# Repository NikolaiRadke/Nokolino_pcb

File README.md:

The ATtiny-based litte brother of Noko. Tiny and cute. And everyone is invited to **contribute**. Nokolino is for everyone. This repository is for the **PCB** version of Nokolino, easy and fast to build. See [PCB](https://github.com/NikolaiRadke/NOKOlino_2/tree/master/PCB.md) on how to get your own boards. Do you own a complete kit? Look [here](https://github.com/NikolaiRadke/Nokolino).    
  
What's new? See the [newsblog](https://github.com/NikolaiRadke/NOKOlino_2/tree/master/NEWS.md).   

Like his big brother **Noko**, the little Nokolino delights it's surroundings with cheeky comments. But unlike Noko he is more obstinate - no radio, a display, no frills. Instead of an Arduino he has a small **ATtiny** microcontroller, only an on-off switch and a big button. But he is small, can stay active for days and is, in contrast to his big brother, very easy to build.  
  
Another useful application option would be to use the hardware without the monster suit as a **music box** in an old used doll to bring it back to modern days, maybe with other sounds or songs.  

What does he to - technically? Whenever you press his button, he will laugh. And when he's just turned on, he says something random randomly every statistically 10 minutes. That's ist. Quite a lot for a stuffed monster!  
  
**Nokolino** stands for **No**ra and Ni**ko**s monster - the appendix **lino** describes the small version.  
  
### Notes for non-German Nokolino makers  
  
Right now, the building wiki, the voice set and the manual are in German. I'll try to translate the wiki and the manual one day. Until then, feel free to ask me for translation, if you need help. **Contribute!** I need an English voice set and English text files. In addition, any other language is welcome, Nokolino is to be cosmopolitan!
  
### Prerequisites
  
Nokolino needs Arduino IDE 1.6.6 or newer (https://www.arduino.cc/en/Main/Software). Copy the folder `Nokolino/src/Nokolino_V30/` for the **JQ6500** module, `Nokolino/src//Nokolino_V31/` for the **JQ8400** module, `Nokolino/src/Nokolino_V32/`for the **DFPlayer** module or `Nokolino/src/Nokolino_V21/` for **older 2018 kits** into your sketch folder and install ATtiny support. See [how to compile](https://github.com/NikolaiRadke/Nokolino_pcb/tree/master/howto_compile) for further instructions. 
  
### Content

```
Nokolino/
├── howto_compile/
|   Manual how compile the sketches in your Arduino IDE.
|
├── linux_uploader/
|   Tool for uploading MP3-files to the JQ6500.
|
├── manual/
|   Nokolino manuals in PDF format.
|
├── mp3/
|   Voice sets for 32MBit- & 16MBit modules in German. English needed? Contribute!
|   ├── Nokolino/
|   |   Male voice sets, spoken by Carsten Caniglia.
|   |   ├── 2MB/
|   |   |   80 files for smaller (16 MBit) modules.
|   |   └── 4MB/
|   |       164 files for recommended (32 MBit) modules.
|   └── Nokolina/
|       Female voice set, spoken by Norma Anthes
|       ├── 2MB/
|       |   80 files for smaller (16 MBit) modules.
|       └── 4MB/
|           164 files for recommended (32 MBit) modules.
|
├── schematics/
|   The circuit diagrams, 3D cab model and sewing pattern.  
|   └── gerber/
|       The gerber files for the PCB to build by your own.
|       ├── V30/
|       |   The gerbers for the JQ6500 module.
|       ├── V31/
|       |   The gerbers for the JQ8400 module.
|       └── V32/
|           The gerbers for the DFPlayer module.
|
└── src/
    ATtiny sketches
    ├── Nokolino_V21/
    |   Old software for old 2018 kits.
    ├── Nokolino_V30/
    |   The sketch for the JQ6500 module.
    ├── Nokolino_V31/
    |   The sketch for the JQ8400 module.
    └── Nokolino_V32/
        The sketch for the DFPlayer module.
```
### Let's get started!

Interested in Nokolino? Great! Let's start here: [German wiki](https://github.com/NikolaiRadke/Nokolino_pcb/wiki).  
English wiki will follow. One day...

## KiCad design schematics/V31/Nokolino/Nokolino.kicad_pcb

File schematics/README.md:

# Schematics

* **Nokolino_V32.pdf** Nokolnio's circuit diagram for the DFPlayer module.
* **Nokolino_V31.pdf** Nokolino's circuit diagram for the JQ8400 module.  
* **Nokolino_V30.pdf** Nokolino's circuit diagram for the JQ6500 module.  
* **M2_button_cab.stl** The 3D model for the button cabs for self printing.  
* **Nokolino_Pattern.pdf** Nokolino's sewing pattern.  
* **/gerber**  The folder for the gerber files needed to print your own PCBs.

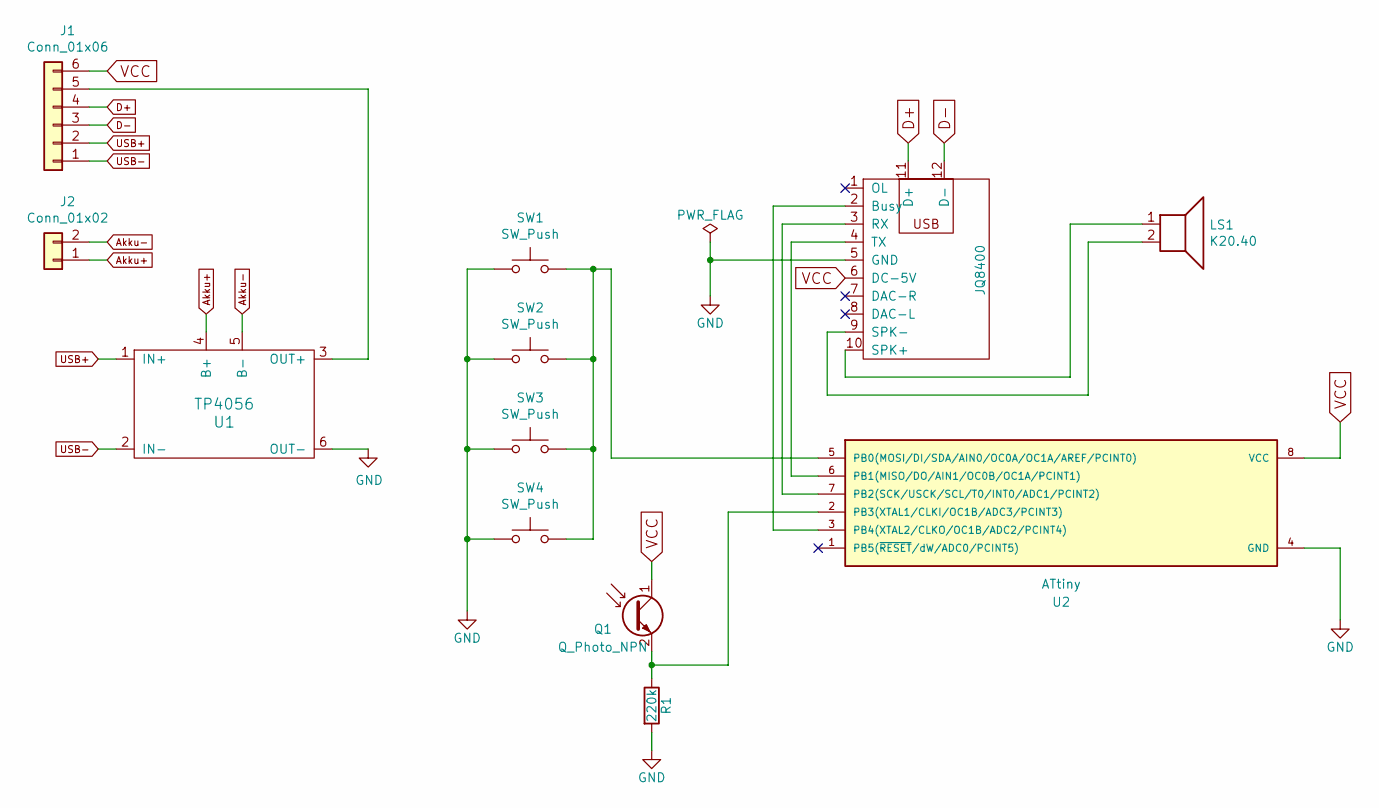
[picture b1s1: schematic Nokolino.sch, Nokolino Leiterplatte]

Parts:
J1: Conn_01x06; PinHeader_1x06_P2.54mm_Vertical
J2: Conn_01x02; PinHeader_1x02_P2.54mm_Vertical
LS1: K20.40
Q1: Q_Photo_NPN; PinHeader_1x02_P2.54mm_Vertical
R1: 220k; R_Axial_DIN0207_L6.3mm_D2.5mm_P7.62mm_Horizontal
SW1, SW2, SW3, SW4: SW_Push; SW_PUSH_6mm_H13mm
U1: TP4056; TP4056-Protect
U2: ATtiny; ATTINY85-20PU
U3: JQ8400; JQ8400-10p

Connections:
Akku+: J2.1, U1.4 (B+)
Akku-: J2.2, U1.5 (B-)
D+: J1.4, U3.11 (D+)
D-: J1.3, U3.12 (D-)
GND: R1.2, SW1.1, SW2.1, SW3.1, SW4.1, U1.6 (OUT-), U2.4 (GND), U3.5 (GND)
unnamed: J1.5, U1.3 (OUT+)
unnamed: LS1.1, U3.10 (SPK+)
unnamed: LS1.2, U3.9 (SPK-)
unnamed: Q1.2 (E), R1.1, U2.2 (PB3(XTAL1/CLKI/OC1B/ADC3/PCINT3))
unnamed: SW1.2, SW2.2, SW3.2, SW4.2, U2.5 (PB0(MOSI/DI/SDA/AIN0/OC0A/OC1A/AREF/PCI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)
unnamed: U2.3 (PB4(XTAL2/CLKO/OC1B/ADC2/PCINT4)), U3.2 (Busy)
unnamed: U2.6 (PB1(MISO/DO/AIN1/OC0B/OC1A/PCINT1)), U3.4 (TX)
unnamed: U2.7 (PB2(SCK/USCK/SCL/T0/INT0/ADC1/PCINT2)), U3.3 (RX)
USB+: J1.2, U1.1 (IN+)
USB-: J1.1, U1.2 (IN-)
VCC: J1.6, Q1.1 (C), U2.8 (VCC), U3.6 (DC-5V)

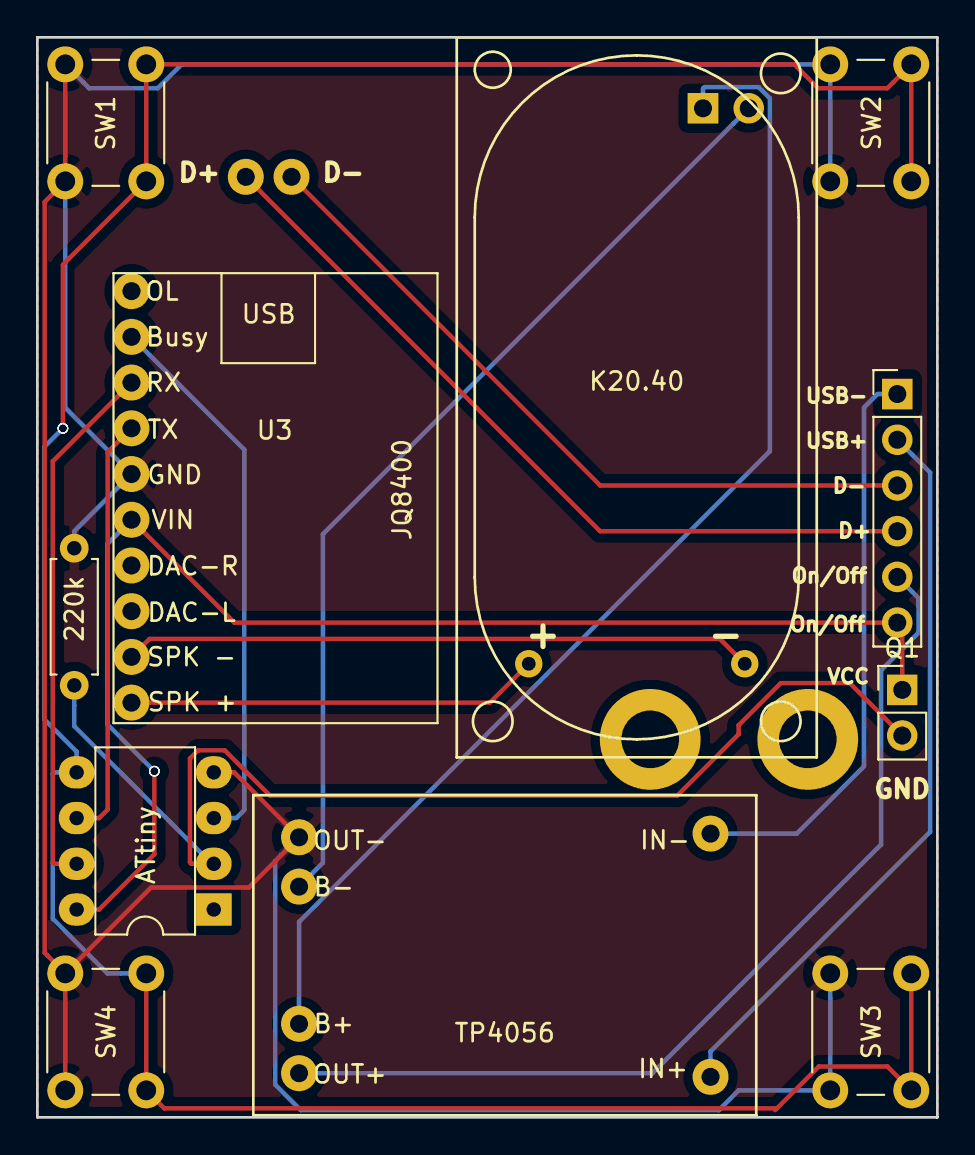
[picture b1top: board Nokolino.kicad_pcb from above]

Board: 2 copper layers, 50.0 x 60.0 mm, 14 parts (1 on the bottom side), 16 nets.

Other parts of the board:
MH1: MH1; MountingHole_3.2mm_M3_DIN965_Pad
MH2: MH2; MountingHole_3.2mm_M3_DIN965_Pad

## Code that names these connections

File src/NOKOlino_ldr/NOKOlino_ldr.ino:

/* NOKOlino V1.0 24.05.2018 - Nikolai Radke
 *  
 *  Sketch for Mini-NOKO-Monster
 *  for Attiny45/85 | 8 Mhz - remember to flash your bootloader first!
 *  SoftwareSerial needs 8 MHz to work correctly.
 *  
 *  Flash-Usage: 3.724 (1.8.2 | ATTiny 1.0.2 | Linux X86_64 | ATtiny85)
 *  
 *  Circuit:
 *  1: RST | PB5  free
 *  2: A3  | PB3  SFH300          
 *  3: A2  | PB4  Busy JQ6500 - 8
 *  4: GND        GND
 *  5: D0  | PB0  free
 *  6: D1  | PB1  RX JQ6500   - 9   
 *  7: D2  | PB2  Button      - GND
 *  8: VCC        VCC
 *  
 *  Sleepmodes:
 *  0=16ms, 1=32ms, 2=64ms, 3=128ms, 4=250ms, 5=500ms
 *  6=1sec, 7=2sec, 8=4sec, 9=8sec
 */

#include <avr/sleep.h>
#include <avr/interrupt.h>
#include <SoftwareSerial.h>
#include <EEPROM.h>

//--------------------------------------------------------------------------------
// Configuation
#define Time         10             // Say something every statistical 10 minutes
#define Volume       25             // Volume 0-30 - 20 is recommended 

#define Breadboard                // Breadboard or PCB?

// Voice set selection
//#define Set_8MBit_16MBit
#define Set_32MBit
//#define Set_own

#ifdef Set_8MBit_16MBit
  #define Button_event 30           // Last button event number (30.mp3)
  #define Time_event   79           // Last time event number (79.mp3)
#endif
#ifdef Set_32MBit
  #define Button_event 40
  #define Time_event   163
#endif
#ifdef Set_own
  #define Button_event 0
  #define Time_event   0
#endif

#ifdef Breadboard
  #define Offset       0.4          // Battery measuring error
  #define maxInput     50           // Max. value from busy line. 
#else
  #define Offset       0.6
  #define maxInput     0
#endif

// Optional - comment out with // to disable
#define Batterywarning             // NOKOlino gives a warning when battery is low
//---------------------------------------------------------------------------------

// Optional battery warning
#define minCurrent   3.50 +Offset   // Low power warning current + measuring error
#define battLow      3.30 +Offset   // Minimal voltage before JQ6500 fails

// Hardware pins
#define TX      0
#define RX      1
#define Busy    2

// ADC and BOD
#ifndef cbi
  #define cbi(sfr, bit) (_SFR_BYTE(sfr) &= ~_BV(bit))
#endif
#ifndef sbi
  #define sbi(sfr, bit) (_SFR_BYTE(sfr) |= _BV(bit))
#endif
#define BODS 7                       // BOD sleep bit in MCUCR
#define BODSE 2                      // BOD sleep enable bit in MCUCR

// Variables
uint16_t address,seed;
volatile boolean f_wdt = 1;          // Volatile -> it is an interrupt routine
boolean low=false;

SoftwareSerial mp3(TX,RX);           // TX to D0, RX to D1

int main(void) {

#ifdef Batterywarning
  uint16_t current;
  double vref;
  uint16_t counter=10;               // Check shortly after startup
#endif

init(); 
{
  // Power saving
  MCUCR |= _BV(BODS) | _BV(BODSE);   // Disable brown out detection - default?
  ACSR |= _BV(ACD);                  // Disable analog comparator - default?
  DDRB &= ~(1<<PB2);                 // D2 INPUT
  PORTB |= (1<<PB2);                 // D2 HIGH 

  pinMode(0,OUTPUT);
  digitalWrite(0,LOW);
  
  // Start JQ6500
  mp3.begin(9600);
  mp3.write("\x7E\x02\x0C\xEF");     // Reset JQ6500
  setup_watchdog(5);                 // Sleep 500ms
  attiny_sleep();                 
  mp3.write("\x7E\x03\x06");
  mp3.write(Volume);                 // Set volume
  mp3.write("\xEF"); 
  setup_watchdog(3);
  attiny_sleep();                    // Sleep 128ms
  mp3.write("\x7E\x03\x11\x04\xEF"); // No loop
  attiny_sleep();                    // Sleep 128ms
  mp3.write("\x7E\x02\x0A\xEF");     // Sleep, JQ6500!

  // Randomize number generator
  address=eeprom_read_word(0);       // Read EEPROM address
  if ((address<2) || (address>(EEPROM.length()-3)))             
  {                                  // Initialize EEPROM and size for first use or after end of cycle
    address = 2;                     // Starting address
    eeprom_write_word(0,address);    // Write starting address
    eeprom_write_word(address,0);    // Write seed 0
  }
  seed=eeprom_read_word(address);    // Read seed
  if (seed>900)                      // After 900 write-cyles move to another address
  {                                  // to keep the EEPROM alive
    seed=0;
    address+=2;
    eeprom_write_word(0,address);
  }
  randomSeed(seed);                  // Randomize
  seed++;                            // New seed
  eeprom_write_word(address,seed);   // Save new seed for next startup
}

// Main loop
while(1)
{
  // Wait for button or time and go to sleep - ~8 times/second         
  if (!low) 
  {
    if (analogRead(3)<20) digitalWrite(0,HIGH);
    else digitalWrite(0,LOW);
    if (!(PINB & (1<<PB2))) JQ6500_play(random(0,Button_event+1));      // Button event
    else if (random(0,Time*60*8)==1) JQ6500_play(random(Button_event+1,Time_event+1)); // Time event
    else attiny_sleep();
  }
  
  // Check current, if defined
  #ifdef Batterywarning
  if (counter==0)                
  {
    current=MeasureVCC();
    vref=1024*1.1f/(double)current;
    if (vref<=minCurrent)            // Current below minimum
    {
      if (vref<=battLow) low=true;   // Power too low for JQ6500
      else JQ6500_play(Time_event+1);// NOKOLINO says "Beep"
    }
    else low=false;
    counter=400;                     // Every minute, 50x 128ms + some sleeping ms
  }
  counter--;
  #endif
}}

void JQ6500_play(uint8_t f)          // Plays MP3 number f
{
  attiny_sleep();                    // Without pause, pull-up messes the busy signal
  mp3.write("\x7E\x04\x03\x01");     // Play file number f
  mp3.write(f);
  mp3.write("\xEF");
  attiny_sleep();
  while (analogRead(A2)>maxInput) attiny_sleep(); // Check busy
  mp3.write("\x7E\x02\x0A\xEF");     // Go back to sleep, JQ6500!
  attiny_sleep();
}

void attiny_sleep()                  // Sleep to save power
{  
  cbi(ADCSRA,ADEN);                  // Switch ADC off
  set_sleep_mode(SLEEP_MODE_PWR_DOWN); 
  sleep_mode();                                         
  sbi(ADCSRA,ADEN);                  // Switch ADC on
}

void setup_watchdog(uint8_t mode)    // Setup wake time
{
  uint8_t bb;
  bb=mode & 7;
  if (mode > 7) bb|= (1<<5);
  bb|= (1<<WDCE);
  MCUSR &= ~(1<<WDRF);
  WDTCR |= (1<<WDCE) | (1<<WDE);
  WDTCR = bb;
  WDTCR |= _BV(WDIE);
}

uint16_t MeasureVCC(void)            // Thank you, Tim!
{
  PRR    &=~_BV(PRADC); 
  ADCSRA  =_BV(ADEN)|_BV(ADPS2)|_BV(ADPS1)|_BV(ADPS0); 
  ADMUX   =_BV(REFS2) | 0x0c; 
  _delay_ms(1);  
  ADCSRA  |=_BV(ADSC);
  while (!(ADCSRA&_BV(ADIF))); 
  ADCSRA  |=_BV(ADIF);
  return ADC;
}

ISR(WDT_vect)                       // Set global flag
{
  f_wdt=1; 
}

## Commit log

2018-05-12 cleanup
2018-05-12 Added new shopping list
2018-05-15 Updated upload tool
2018-05-15 Updated upload an repair software
2018-05-22 Smoother pattern graphic
2018-05-22 Updated shopping list
2018-05-23 Added 16Mbit module support
2018-05-24 Better data compression for 16MBit set
2018-05-27 Set 16Mbit set as default
2018-06-16 Updated linux uploader
2018-06-29 Improved power saving when battery is low
2018-08-21 Updated linux upload tool
2018-08-31 Optimized PCB battery warning settings
2018-09-01 Oops - wrong mp3 module preset
2018-09-05 New schematics and a new phototransistor feature!
2018-09-22 New Firmware 220918
2018-09-24 Disabled analog comparator again
2018-09-25 Firmware 250918
2018-10-05 Added both 1.0 and new (undocumented) 1.1 version
2018-10-19 New jq6500 upload tool
2019-01-15 Reworked volume control
2019-04-05 updated mp3 uploader
2019-04-16 Firmware 160419 - fixed a dark mode bug
2019-04-16 New schematics for upcoming version V3.0
2019-04-17 Removed wrong drill map in gerber files
2019-05-12 Reworked new V3 PCB gerber files
2019-08-03 NOKOlino goes into upload mode when button is pressed at startup
2019-08-03 Firmware 2.1-030819 and 3.0-030819
2019-08-08 Fixed stupid typo
2019-08-27 New linux uploader
2019-12-30 New V3.0 firmware. Hardware PCB will follow soon.
2020-01-01 New V30 PCB files
2020-01-02 Updated V30 drill file. Just a cosmetic correction.
2020-01-02 V30: Reduced flash size but alas it is still too large for ATtiny45
2020-01-03 New firmware 3.0-031020 which fits into ATtiny45!
2020-01-25 New V3.0 PCB design
2020-02-11 New V31 version für jq8400 modules added.
2020-02-11 Updated firmware V3.0-110220
2020-02-11 Updated firmware V3.1-110220
2020-02-14 Renewed top PCB design for new 3D printedbutton caps and optional phototransistor
2020-02-14 Added STL file for 3D printed M2 button caps
2020-03-09 Slightly updated top PCB
2020-03-10 Updated V3.1 schematics
2020-05-09 Updated V31 firmware 090529
2020-05-29 Updated sewing pattern
2020-06-04 New manual
2020-06-06 Updated manuals
2020-06-12 updated V30 gerber file
2020-06-25 Firmware 3.1-250620
2020-06-27 Added old V21 for old kit support
2020-06-27 Added support for older V21 kit version
2020-09-30 Added new V3.2 Nokolino
2020-10-02 Code cleanup
2022-01-28 V3.2 now supports all DFPlayers an battery warning
2022-02-05 Added V3.1 version for Digispark modules
2022-02-07 Added setch fot V3.1 Digispark support
2022-04-25 Refresh
2022-04-28 Fixed errors in comments
2023-03-18 Fixed old battery low flag bug
2023-03-31 New deep sleep mode for V3.2
